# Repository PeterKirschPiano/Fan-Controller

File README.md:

# General
A Fan Controller that uses pwm of 20khz to be inaudible. 
It controlls the fan and uses a DS18B20 to check the surrounding temperature. 
The Controller allows for a Thermostate Mode indicated by a flashind LED.

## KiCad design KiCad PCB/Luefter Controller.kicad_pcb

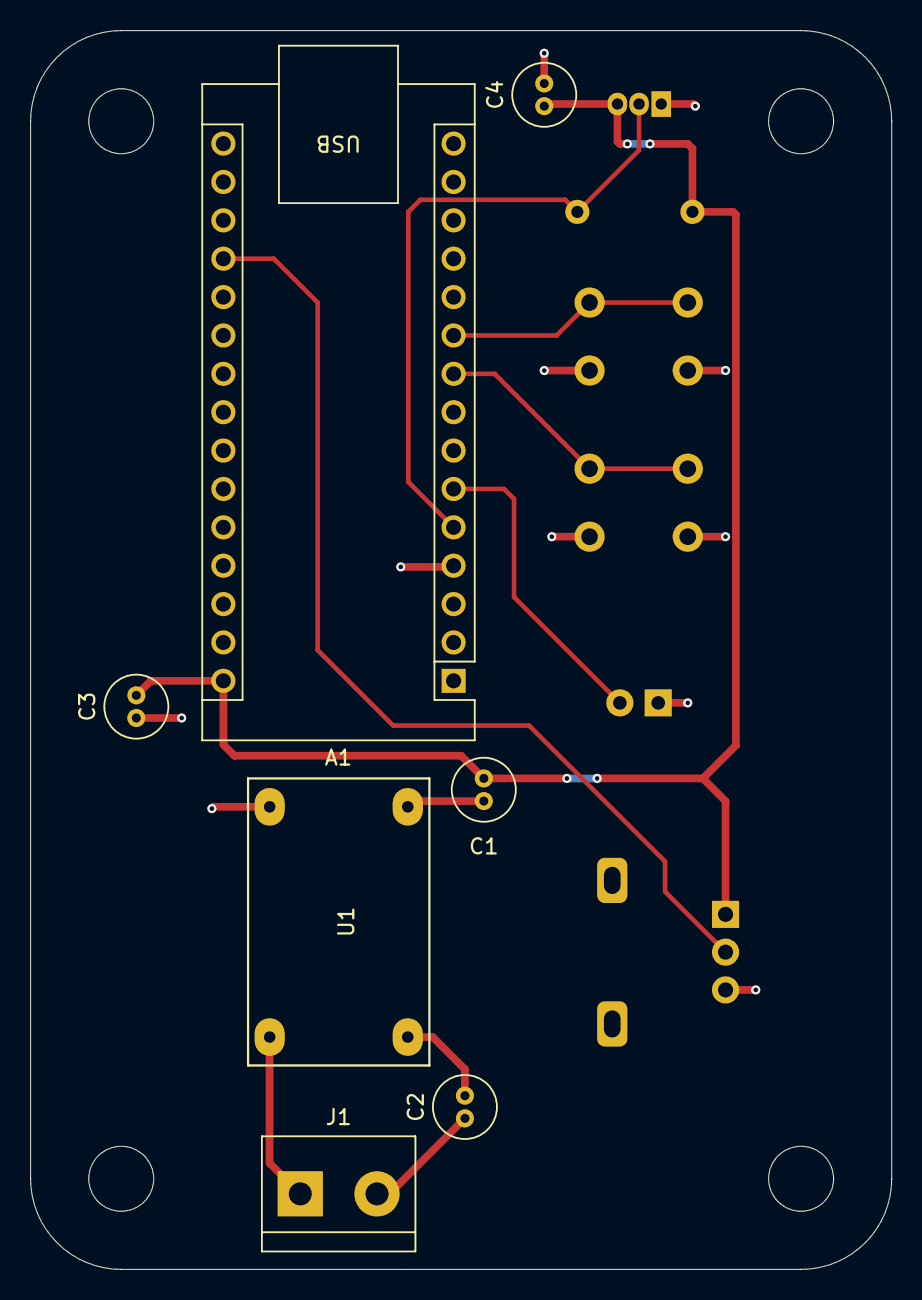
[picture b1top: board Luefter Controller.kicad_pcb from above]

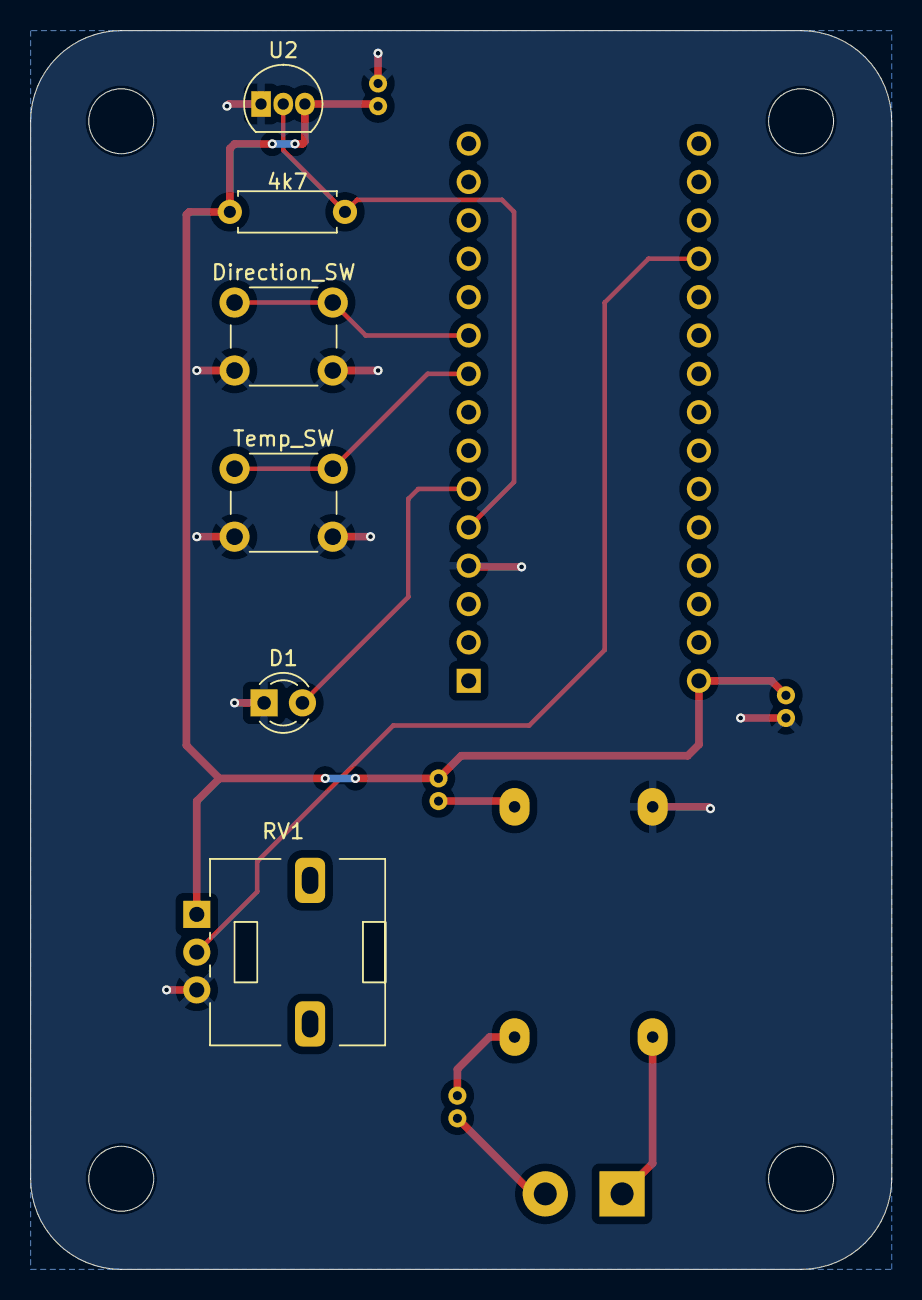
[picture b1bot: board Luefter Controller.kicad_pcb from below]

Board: 2 copper layers, 57.0 x 82.0 mm, 17 parts (6 on the bottom side), 11 nets.

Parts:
A1: Arduino_Nano_v3.x; Arduino_Nano
C1, C2: C10; C_Radial_D4.0mm_H7.0mm_P1.50mm
C3, C4: C100; C_Radial_D4.0mm_H7.0mm_P1.50mm
D1: LED; LED_D3.0mm
Direction_SW: SW_Push; SW_PUSH_6mm_H13mm
H1, H2, H3, H4: MountingHole; MountingHole_4.3mm_M4
J1: Screw_Terminal_2P; TerminalBlock_bornier-2_P5.08mm
R1: 4k7; R_Axial_DIN0207_L6.3mm_D2.5mm_P7.62mm_Horizontal
RV1: R_Potentiometer; Potentiometer_Alps_RK09L_Single_Vertical
Temp_SW: SW_Push; SW_PUSH_6mm_H13mm
U1: Mini360; Mini360_step-down
U2: DS18B20; TO-92_Inline

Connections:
+5V: A1.30 (VIN), C1.2, C3.2, C4.1, R1.2, RV1.1, U2.3 (V_{DD})
/A0_POT: A1.19 (A0), RV1.2
/D2_DS18B20: A1.5 (D2), R1.1, U2.2 (DQ)
/D3_LED: A1.6 (D3), D1.2 (A)
/D6_BUTTON_DIRECT: A1.10 (D7), Direction_SW.1
/D6_BUTTON_TEMP: A1.9 (D6), Temp_SW.1
GND: A1.4 (GND), C3.1, C4.2, D1.1 (K), Direction_SW.2, RV1.3, Temp_SW.2, U1.3 (OUT-), U2.1 (GND)
unnamed: J1.1, U1.1 (IN-)
unnamed: C2.1, J1.2
unnamed: C2.2, U1.2 (IN+)
unnamed: C1.1, U1.4 (OUT+)

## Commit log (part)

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2025-04-16 Create ASD
2025-08-07 Create Pictures-Videos
2025-08-07 Rename IMG20250807091709.jpg to Pictures-Videos/IMG20250807091709.jpg
2025-08-07 Rename IMG20250807091720.jpg to Pictures-Videos/IMG20250807091720.jpg
2025-08-07 Rename IMG20250807094252.jpg to Pictures-Videos/IMG20250807094252.jpg
2025-08-07 Rename IMG20250807094301.jpg to pictures-videos/IMG20250807094301.jpg
2025-08-07 Rename IMG20250807094408.jpg to Pictures-Videos /IMG20250807094408.jpg
2025-08-07 Rename IMG20250807094418.jpg to Pictures-Videos /IMG20250807094418.jpg
2025-08-07 Rename IMG20250807094605.jpg to Pictures-Videos/IMG20250807094605.jpg
2025-08-07 Rename IMG20250807094725.jpg to Pictures-Videos/IMG20250807094725.jpg
2025-08-07 Rename IMG20250807094738.jpg to Pictures-Videos/IMG20250807094738.jpg
2026-03-20 Add project description to README.md
